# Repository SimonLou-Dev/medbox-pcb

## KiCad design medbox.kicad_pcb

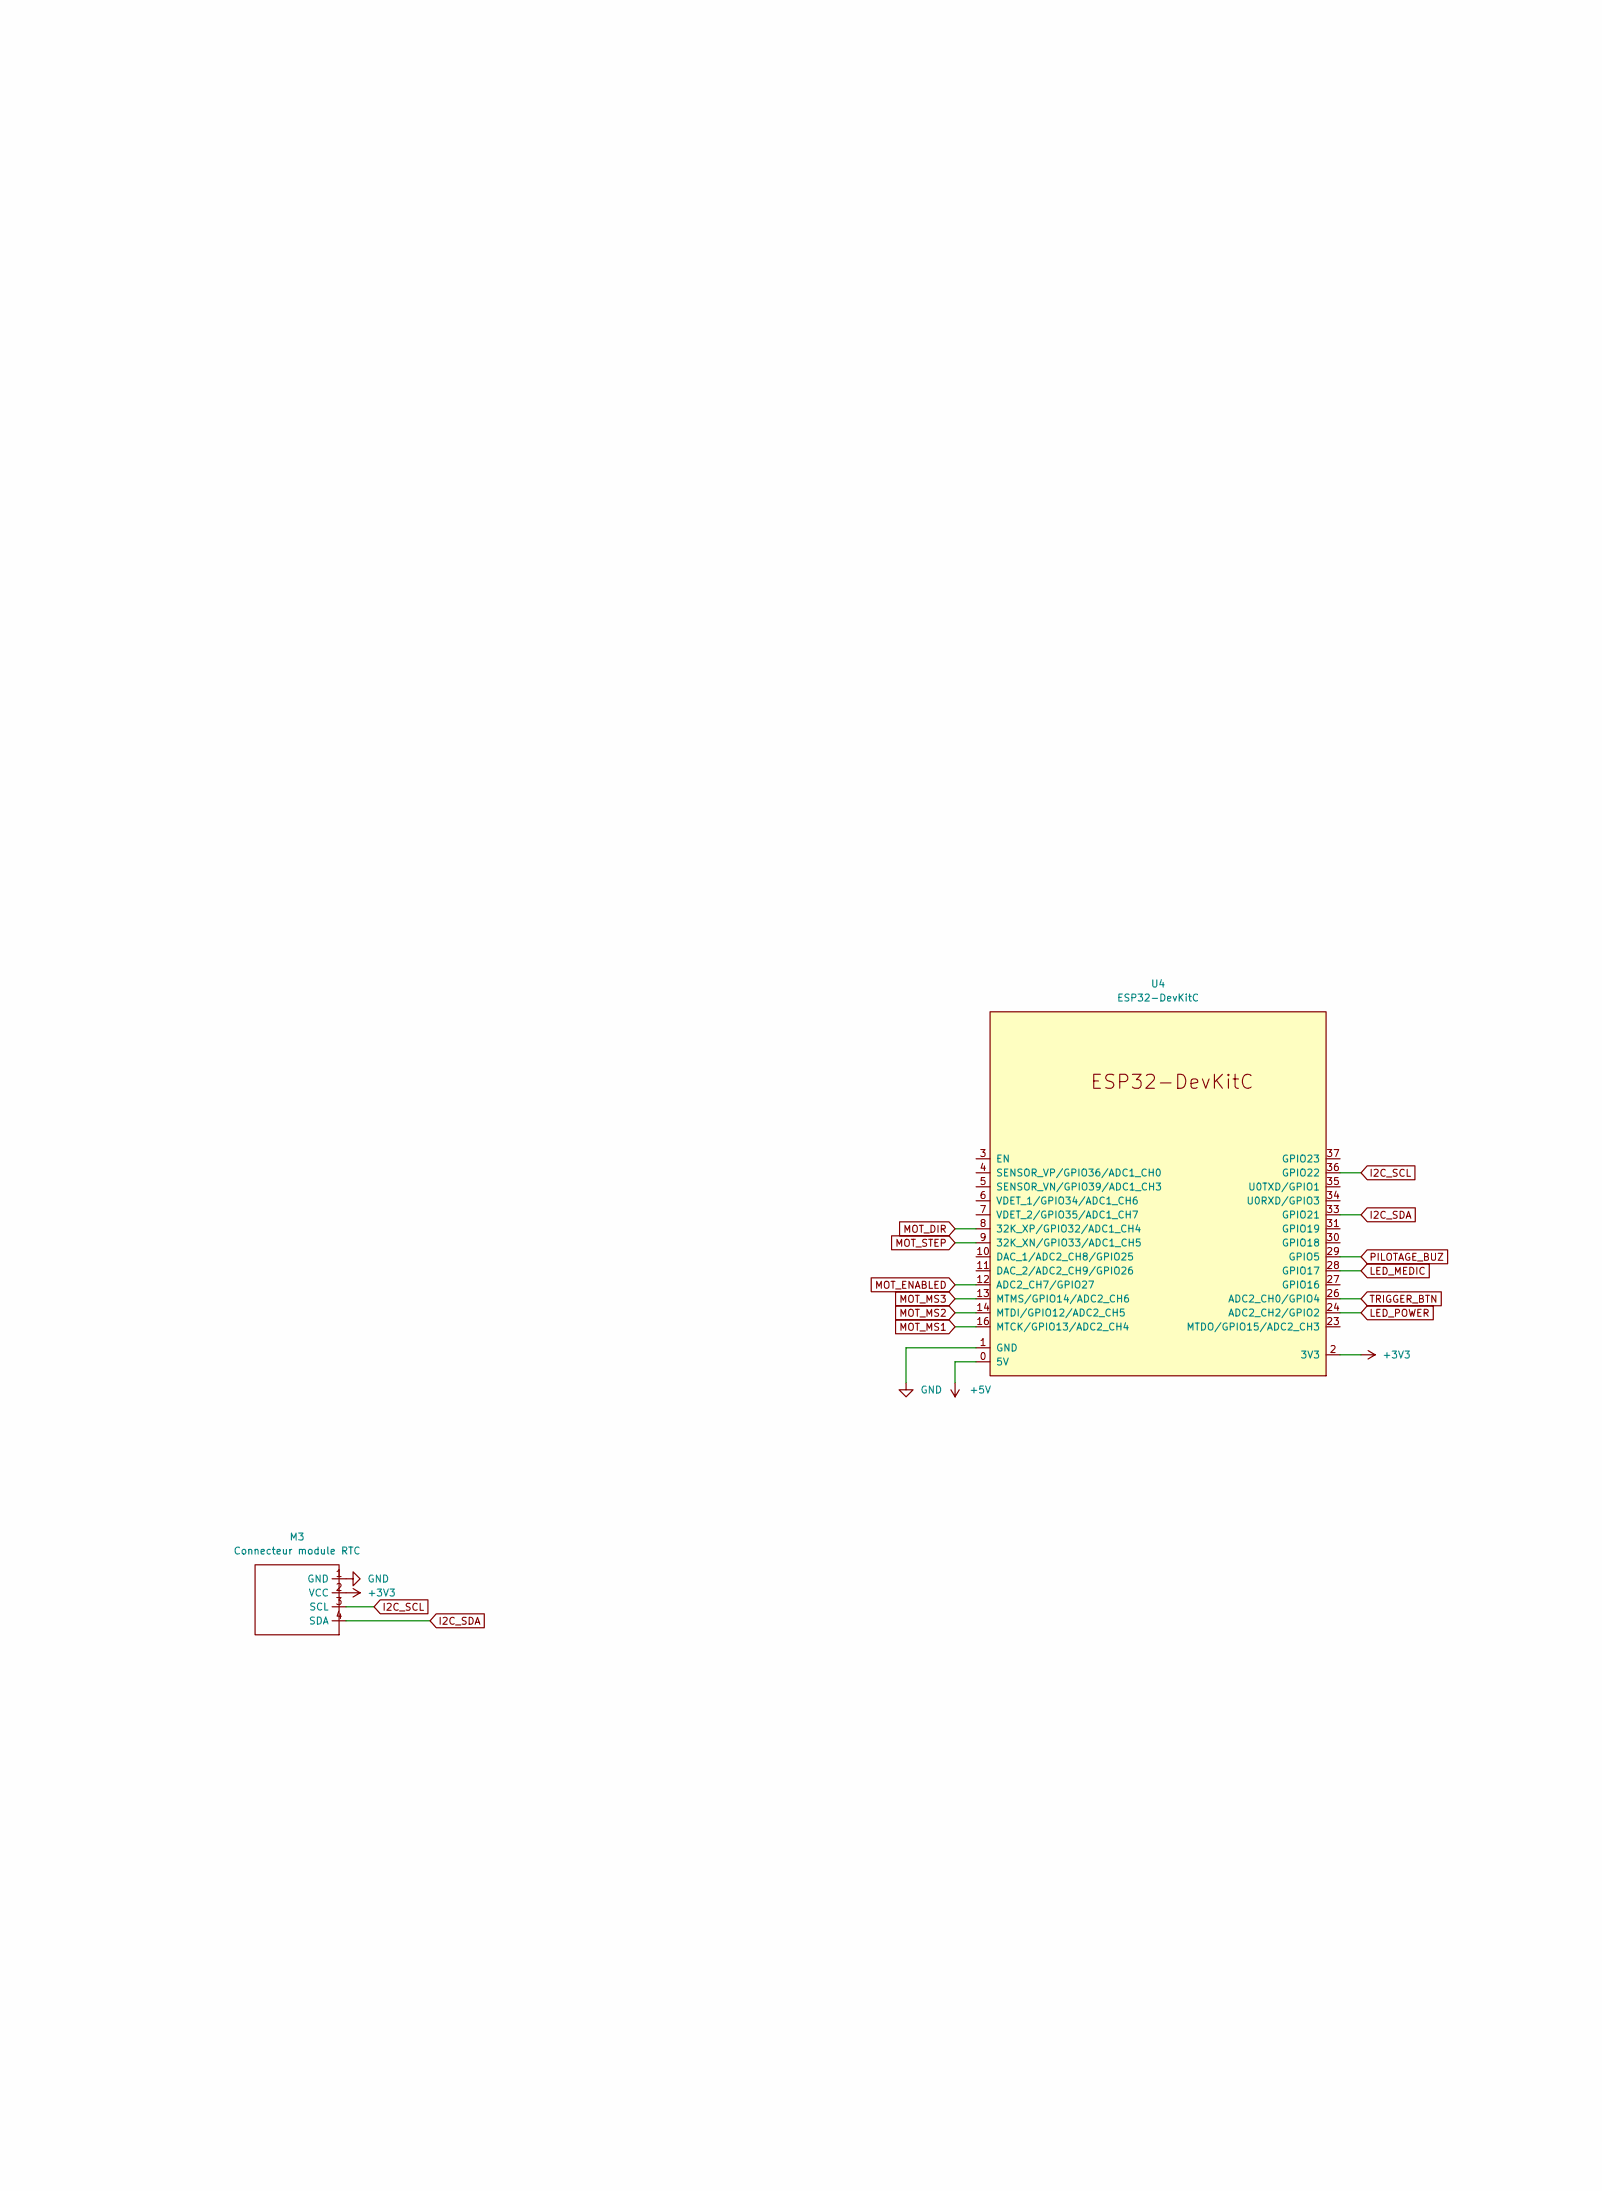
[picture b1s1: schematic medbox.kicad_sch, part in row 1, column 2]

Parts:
M3: Connecteur module RTC; PinSocket_1x04_P2.54mm_Vertical
U4: ESP32-DevKitC

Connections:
+3V3: M3.2 (VCC), U4.2 (3V3); also elsewhere on the board
+5V: U4.0 (5V); also elsewhere on the board
GND: M3.1 (GND), U4.1 (GND); also elsewhere on the board
I2C_SCL: M3.3 (SCL), U4.36 (GPIO22)
I2C_SDA: M3.4 (SDA), U4.33 (GPIO21)
LED_MEDIC: U4.28 (GPIO17); also elsewhere on the board
LED_POWER: U4.24 (ADC2_CH2/GPIO2); also elsewhere on the board
MOT_DIR: U4.8 (32K_XP/GPIO32/ADC1_CH4); also elsewhere on the board
MOT_ENABLED: U4.12 (ADC2_CH7/GPIO27); also elsewhere on the board
MOT_MS1: U4.16 (MTCK/GPIO13/ADC2_CH4); also elsewhere on the board
MOT_MS2: U4.14 (MTDI/GPIO12/ADC2_CH5); also elsewhere on the board
MOT_MS3: U4.13 (MTMS/GPIO14/ADC2_CH6); also elsewhere on the board
MOT_STEP: U4.9 (32K_XN/GPIO33/ADC1_CH5); also elsewhere on the board
PILOTAGE_BUZ: U4.29 (GPIO5); also elsewhere on the board
TRIGGER_BTN: U4.26 (ADC2_CH0/GPIO4); also elsewhere on the board

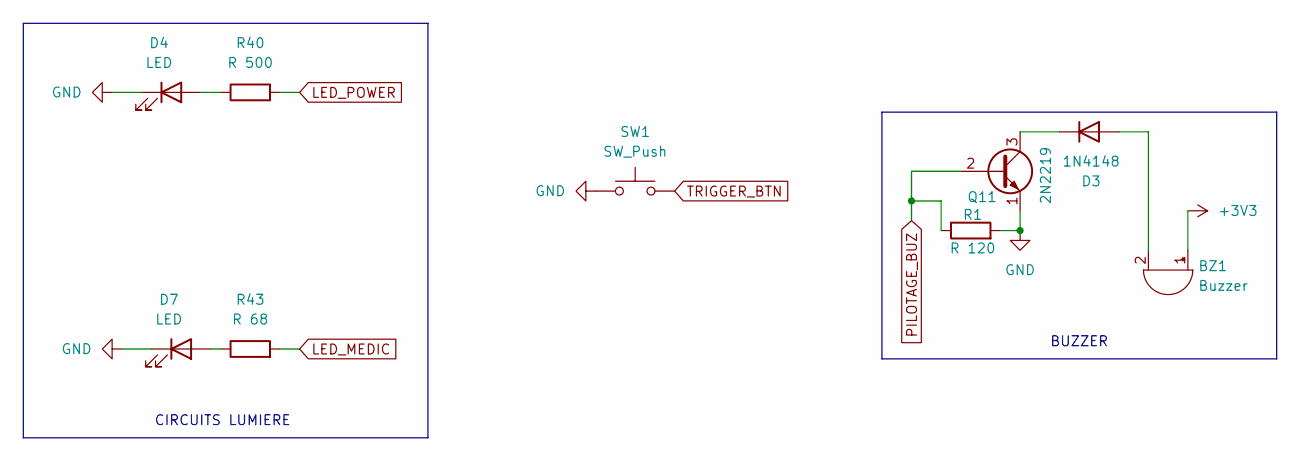
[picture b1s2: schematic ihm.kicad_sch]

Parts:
BZ1: Buzzer; buzzer
D3: 1N4148; D_DO-35_SOD27_P7.62mm_Horizontal
D4: LED; LED_D3.0mm
D7: LED; LED_D5.0mm
Q11: 2N2219; TO-39-3
R1: R 120; R_Axial_DIN0207_L6.3mm_D2.5mm_P7.62mm_Horizontal
R40: R 500; R_Axial_DIN0207_L6.3mm_D2.5mm_P7.62mm_Horizontal
R43: R 68; R_Axial_DIN0207_L6.3mm_D2.5mm_P7.62mm_Horizontal
SW1: SW_Push; SW_PUSH_6mm_H7.3mm

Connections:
+3V3: BZ1.1 (+); also elsewhere on the board
GND: D4.1 (K), D7.1 (K), Q11.1 (E), R1.2, SW1.1; also elsewhere on the board
LED_MEDIC: R43.2; also elsewhere on the board
LED_POWER: R40.2; also elsewhere on the board
unnamed: BZ1.2 (-), D3.2 (A)
unnamed: D3.1 (K), Q11.3 (C)
unnamed: D4.2 (A), R40.1
unnamed: D7.2 (A), R43.1
PILOTAGE_BUZ: Q11.2 (B), R1.1; also elsewhere on the board
TRIGGER_BTN: SW1.2; also elsewhere on the board

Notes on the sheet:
BUZZER
CIRCUITS LUMIERE

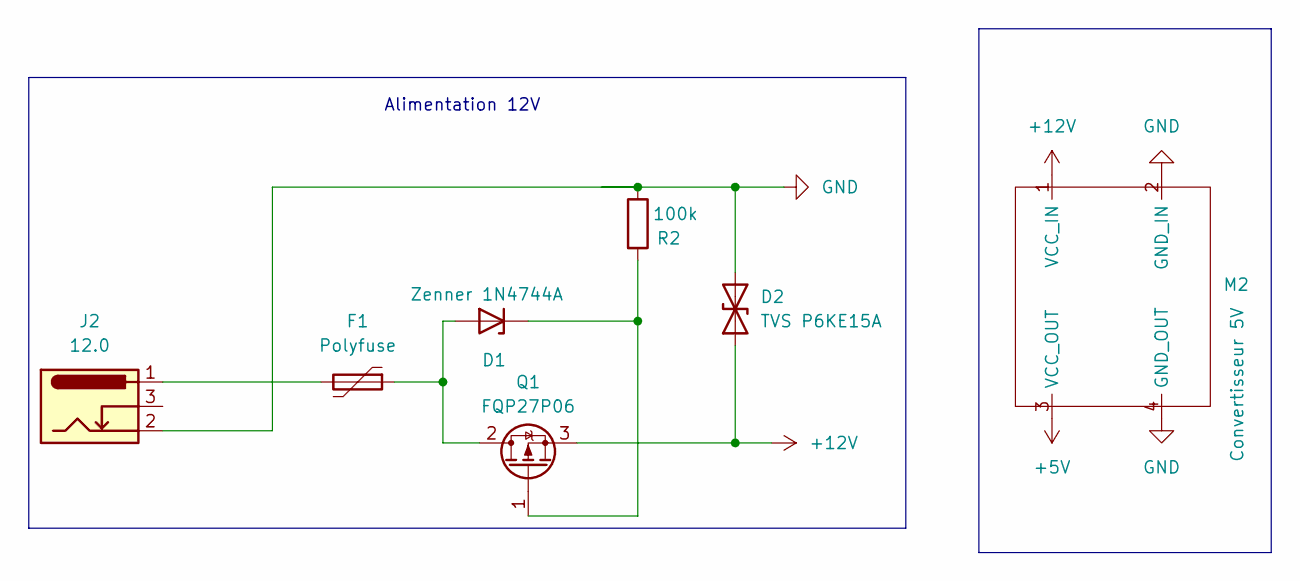
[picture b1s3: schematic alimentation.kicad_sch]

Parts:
D1: Zenner 1N4744A; D_DO-41_SOD81_P7.62mm_Horizontal
D2: TVS P6KE15A; D_SMB_Handsoldering
F1: Polyfuse; Fuse_Littelfuse_395Series
J2: 12.0; BarrelJack_GCT_DCJ200-10-A_Horizontal
M2: Convertisseur 5V; MP1584EN
Q1: FQP27P06; TO-220-3_Vertical
R2: 100k; R_Axial_DIN0207_L6.3mm_D2.5mm_P7.62mm_Horizontal

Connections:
+5V: M2.3 (VCC_OUT); also elsewhere on the board
+12V: D2.1 (A1), M2.1 (VCC_IN), Q1.3 (S); also elsewhere on the board
GND: D2.2 (A2), J2.2, M2.2 (GND_IN), M2.4 (GND_OUT), R2.1; also elsewhere on the board
unnamed: D1.2 (A), F1.1, Q1.2 (D)
unnamed: D1.1 (K), Q1.1 (G), R2.2
unnamed: F1.2, J2.1

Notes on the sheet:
Alimentation 12V

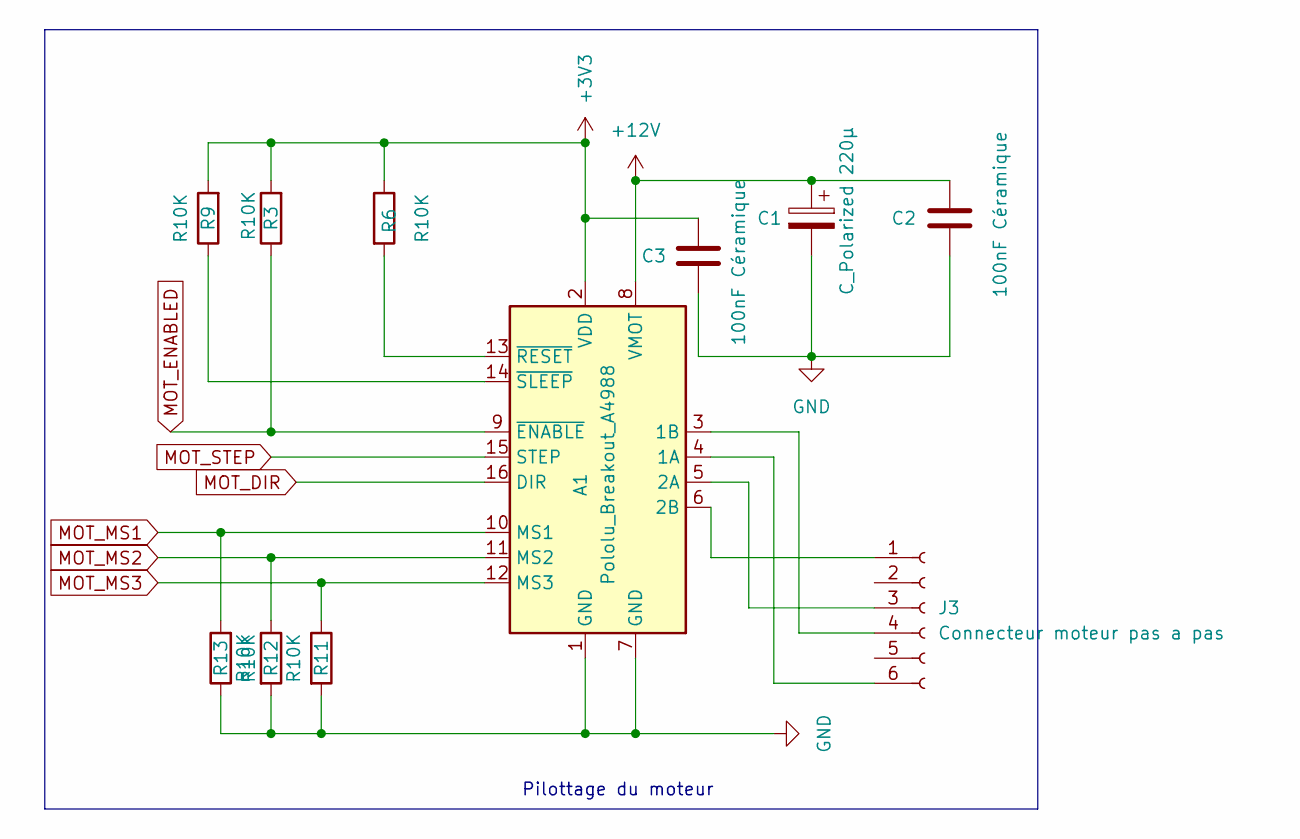
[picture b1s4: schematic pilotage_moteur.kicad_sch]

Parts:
A1: Pololu_Breakout_A4988; Pololu_Breakout-16_15.2x20.3mm
C1: C_Polarized 220µ; CP_Radial_D10.0mm_P5.00mm
C2, C3: 100nF Céramique; C_Disc_D6.0mm_W2.5mm_P5.00mm
J3: Connecteur moteur pas a pas; JST_PH_B6B-PH-K_1x06_P2.00mm_Vertical
R3, R6, R9, R11, R12, R13: R10K; R_Axial_DIN0207_L6.3mm_D2.5mm_P7.62mm_Horizontal

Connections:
+3V3: A1.2 (VDD), C3.1, R3.2, R6.1, R9.2; also elsewhere on the board
+12V: A1.8 (VMOT), C1.1, C2.2; also elsewhere on the board
GND: A1.1 (GND), A1.7 (GND), C1.2, C2.1, C3.2, R11.2, R12.2, R13.1; also elsewhere on the board
MOT_DIR: A1.16 (DIR); also elsewhere on the board
MOT_ENABLED: A1.9 (~ENABLE), R3.1; also elsewhere on the board
MOT_MS1: A1.10 (MS1), R13.2; also elsewhere on the board
MOT_MS2: A1.11 (MS2), R12.1; also elsewhere on the board
MOT_MS3: A1.12 (MS3), R11.1; also elsewhere on the board
MOT_STEP: A1.15 (STEP); also elsewhere on the board
unnamed: A1.4 (1A), J3.6
unnamed: A1.3 (1B), J3.4
unnamed: A1.5 (2A), J3.3
unnamed: A1.6 (2B), J3.1
unnamed: A1.13 (~RESET), R6.2
unnamed: A1.14 (~SLEEP), R9.1

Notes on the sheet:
Pilottage du moteur

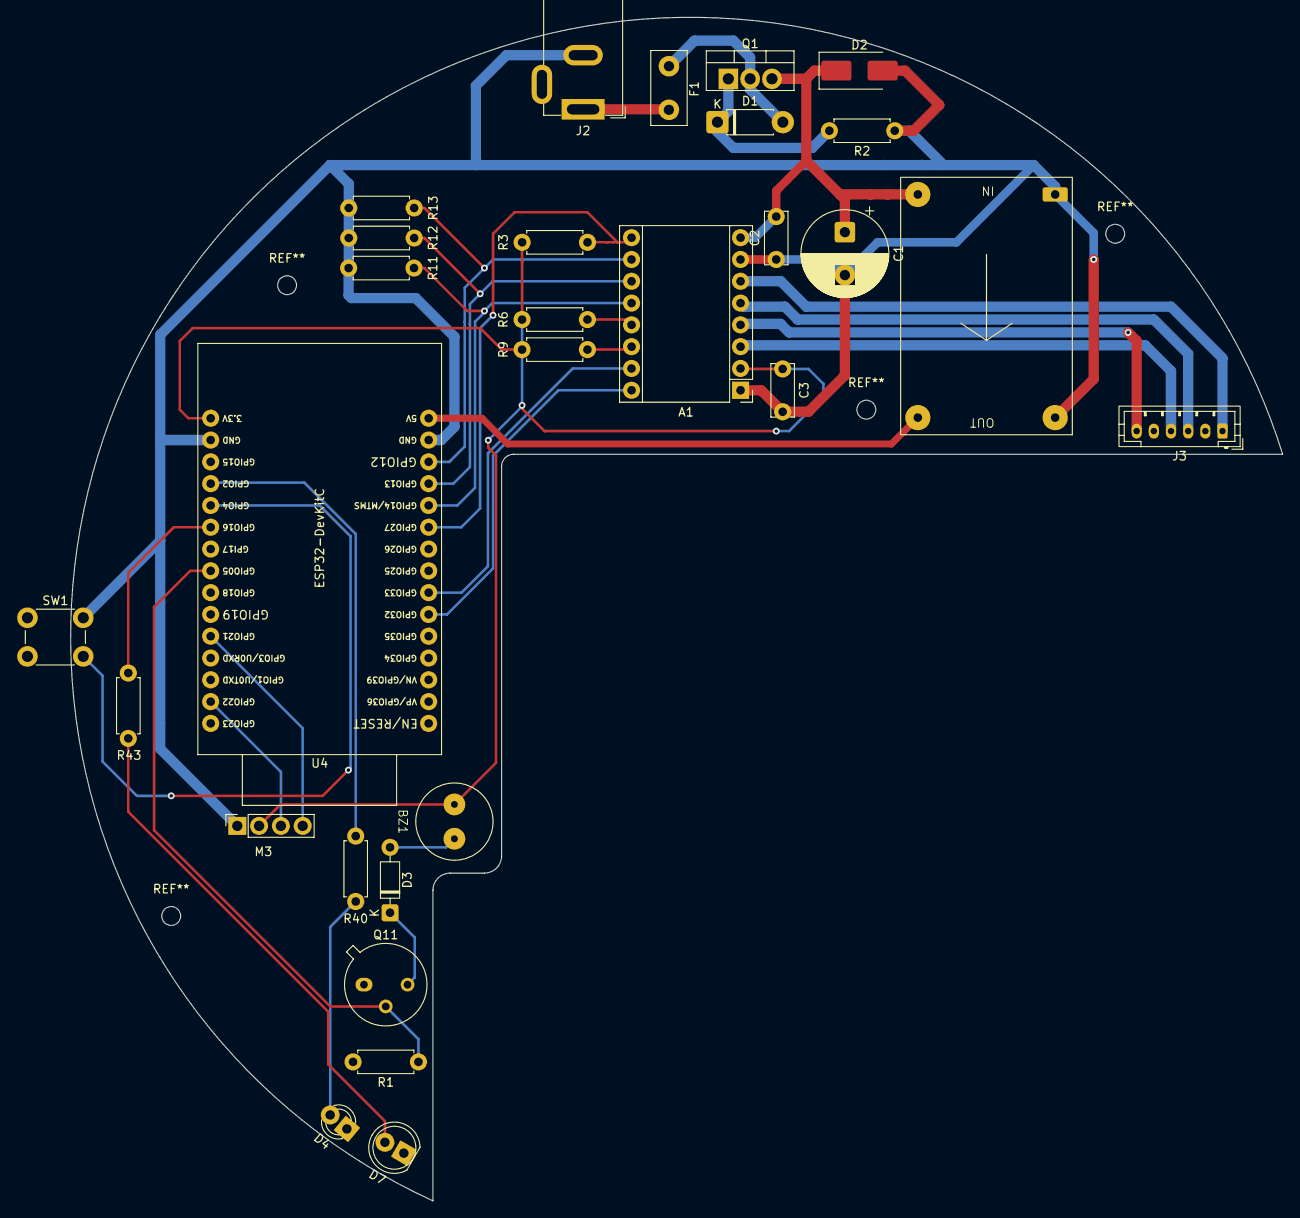
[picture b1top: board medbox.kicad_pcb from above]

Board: 2 copper layers, 141.2 x 137.9 mm, 29 parts (0 on the bottom side), 29 nets.

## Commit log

2026-04-18 update pcb
2026-06-10 PCB me parrait OK
